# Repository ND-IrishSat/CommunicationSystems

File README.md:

# Communication Systems
Created during the fall of 2024, this is an extension to our SDR repo. This is a more updated repo where the development on the sidekiq and usrp takes place.

# Parameters
- test frequencies
    - 70cm | 418274940 Hz | 420 MHz
- Actual frequencies
    - Rx:
    - Tx:
- Hardware
    - amplifiers?
    - antennas

S-Band downlink, but we do not have permission
UHF uplink

Rylan - General liscense

Sidekiq: ports 1 and 2 are received between 50 MHz and 6 GHz
        Port 3 receive or transmit 50 MHz and 6 GHz

Copy to irishsat    
    $ scp -r ~/path/CommunicationSystems/ irishsat:~/Documents/Github/

To compile test apps in the test folder on irishsat desktop run:
        $ make BUILD_CONFIG=arm_cortex-a9.gcc7.2.1_gnueabihf
        Add clean after to clean builds
        This will build the test files in the bin folder

root@sidekiqz2:/tmp# ./rx_samples -d output --words 5000000 --rate 1000000000 --frequency 418274940

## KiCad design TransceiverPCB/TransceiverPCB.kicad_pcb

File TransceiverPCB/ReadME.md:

```
 /$$$$$$ /$$$$$$$  /$$$$$$  /$$$$$$  /$$   /$$  /$$$$$$   /$$$$$$  /$$$$$$$$                                                            
|_  $$_/| $$__  $$|_  $$_/ /$$__  $$| $$  | $$ /$$__  $$ /$$__  $$|__  $$__/                                                            
  | $$  | $$  \ $$  | $$  | $$  \__/| $$  | $$| $$  \__/| $$  \ $$   | $$                                                               
  | $$  | $$$$$$$/  | $$  |  $$$$$$ | $$$$$$$$|  $$$$$$ | $$$$$$$$   | $$                                                               
  | $$  | $$__  $$  | $$   \____  $$| $$__  $$ \____  $$| $$__  $$   | $$                                                               
  | $$  | $$  \ $$  | $$   /$$  \ $$| $$  | $$ /$$  \ $$| $$  | $$   | $$                                                               
 /$$$$$$| $$  | $$ /$$$$$$|  $$$$$$/| $$  | $$|  $$$$$$/| $$  | $$   | $$                                                               
|______/|__/  |__/|______/ \______/ |__/  |__/ \______/ |__/  |__/   |__/                                                               
                                                                                                                                        
                                                                                                                                        
                                                                                                                                        
 /$$$$$$$$                                                         /$$                                     /$$$$$$$   /$$$$$$  /$$$$$$$ 
|__  $$__/                                                        |__/                                    | $$__  $$ /$$__  $$| $$__  $$
   | $$  /$$$$$$  /$$$$$$  /$$$$$$$   /$$$$$$$  /$$$$$$$  /$$$$$$  /$$ /$$    /$$ /$$$$$$   /$$$$$$       | $$  \ $$| $$  \__/| $$  \ $$
   | $$ /$$__  $$|____  $$| $$__  $$ /$$_____/ /$$_____/ /$$__  $$| $$|  $$  /$$//$$__  $$ /$$__  $$      | $$$$$$$/| $$      | $$$$$$$ 
   | $$| $$  \__/ /$$$$$$$| $$  \ $$|  $$$$$$ | $$      | $$$$$$$$| $$ \  $$/$$/| $$$$$$$$| $$  \__/      | $$____/ | $$      | $$__  $$
   | $$| $$      /$$__  $$| $$  | $$ \____  $$| $$      | $$_____/| $$  \  $$$/ | $$_____/| $$            | $$      | $$    $$| $$  \ $$
   | $$| $$     |  $$$$$$$| $$  | $$ /$$$$$$$/|  $$$$$$$|  $$$$$$$| $$   \  $/  |  $$$$$$$| $$            | $$      |  $$$$$$/| $$$$$$$/
   |__/|__/      \_______/|__/  |__/|_______/  \_______/ \_______/|__/    \_/    \_______/|__/            |__/       \______/ |_______/ 
                                                                                                                                        
                                                                                                                                        
                                                                                                                                        
```

### Team

```
├── Communication Systems
│   ├── Rylan Paul
│   ├── Joaquin Caraveo
│   ├── Caden Niziol
│   ├── Alyssa Riter
│   ├── Anna Arnett
│   ├── Thomas Mancini

```

### To Add a New Part

> ----
>
> 1. Open a new github branch from main named `Import PART#`
> 
> 2. Download symbol, footprints, and 3d model (Ultra Librarian, Snap Magic, etc.)
>
> 3. Unzip the files
>
> 4. Structure the folder as shown for `EXAMPLE_PART_ID`
>
> 5. Put the new part folder in the `PARTS` folder
>
> 6. Copy all of the new footprints and paste them into the `LIB_IRISHSAT.pretty` folder
>
> 7. If KiCAD is open, in the footprint editor, press the referesh button
>
> 8. Open the KiCAD Symbol Editor
>
> 9. Search for `LIB_IRISHSAT`
>
> 10. Right click `LIB_IRISHSAT` and click `Import Symbol`
>
> 11. Go to your new part in the `PARTS` folder
>
> 12. Click on the `part.kicad_sym` or `part.lib` file to import it
>
> 13. Close the symbol editor and `save`
>
> 14. Open the `footprint editor`
>
> 15. Go to the newly added footprints
>
> 16. Click the `Footprint Properties` button
>
> 17. Click on the `3D Models` tab
>
> 18. Click the folder icon and navigate to your new part in the `PARTS` folder
>
> 19. Select your 3D model usually either `.stl` or `.stp` or `.step`
>
> 20. Confirm the position and rotation alignment
> 
> 21. Save and close the footprint editor
> 
> 22. Create a `Pull Request` merging your new branch `Import PART#` into `main` and assign your team lead
>
> ----

### Project File Structure

```

├── fp-info-cache
├── fp-lib-table
├── LIB_IRISHSAT.bak
├── LIB_IRISHSAT.kicad_sym                          # All Imported Symbols Library
├── LIB_IRISHSAT.pretty                             # List of all footprints from the `PARTS` folder
│   ├── ...
├── PARTS                                           # List of all parts
│   ├── EXAMPLE_PART_ID                             # Part name
│   │   ├── part.kicad_sym                          # Sybmol file
│   │   ├── part.step                               # 3D Model
│   │   └── footprints.pretty                       # Footpints
│   │       └── part.kicad_mod                      # Footprint files
|   |
│   ├── ABM8_272_T3                                 # Crystal Oscillator 12MHz for RP2040
│   │   ├── ...
│   ├── AD9218BSTZ-65                               # Analog to Digital Converter
│   │   ├── ...
│   ├── AD9763ASTZ                                  # Digital to Analog Converter
│   │   ├── ...
│   ├── ADA4940_2ACPZ_R7                            # Fully Differential Amplifier (ADC Driver)
│   │   ├── ...
│   ├── ADF4351BCPZ-RL7                             # Local Oscillator
│   │   ├── ...
│   ├── ADL5320ARKZ_R7                              # Power Amplifier
│   │   ├── ...
│   ├── ADL5375_05ACPZ_R7                           # IQ Modulator
│   │   ├── ...
│   ├── ADL5380ACPZ_R7                              # IQ Demodulator
│   │   ├── ...
│   ├── B39921B2672P810                             # Band Pass Filter (ISM 915MHz)
│   │   ├── ...
│   ├── BLM18KG601SN1D                              # Ferrite Capacitor
│   │   ├── ...
│   ├── CFR_25JB_52_43R                             # 43 Ohm Resistor ±5%
│   │   ├── ...
│   ├── DSC1001CI2-100-0000T                        # Crystal Oscillator 100MHz for FPGA
│   │   ├── ...
│   ├── QPL6220QTR7                                 # Low Noise Amplifier
│   │   ├── ...
│   ├── W25Q32JVSSIQ                                # Flash Memory QSPI
│   │   ├── ...
│   └── XC7A35T_1FTG256C                            # FPGA
│       ├── ...
├── ReadME.md                                       # ReadMe
├── sym-lib-table
├── TransceiverPCB-backups
│   ├── TransceiverPCB-2026-02-07_141501.zip
│   ├── TransceiverPCB-2026-02-08_221813.zip
│   └── TransceiverPCB-2026-02-08_225630.zip
├── TransceiverPCB.kicad_pcb                        # Main KiCAD file
├── TransceiverPCB.kicad_prl                        # Main KiCAD file
├── TransceiverPCB.kicad_pro                        # Main KiCAD file
└── TransceiverPCB.kicad_sch                        # Main KiCAD file

```

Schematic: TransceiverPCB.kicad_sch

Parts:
C1, C2, C6, C7, C26, C75, C77, C82, C87, C89, C116, C121, C122, C123, C129, C130, C131, C132, C133, C134, C135, C142, C152, C156: 0.1uF; C_0603_1608Metric
C3, C4: 22nF; C_0402_1005Metric
C5, C8, C48, C49, C51, C59: 100pF; C_0402_1005Metric
C9, C14, C15, C16, C17, C18, C19, C20, C22, C23, C30, C35, C70, C79: 100nF; C_0603_1608Metric
C10, C11, C85: 22pF; C_0402_1005Metric
C12, C29, C31, C32, C33, C34, C61: 10uF; C_0603_1608Metric
C13, C21, C24, C25, C36, C44, C45, C55, C56, C90: 1uF; C_0603_1608Metric
C27, C69, C73: 4.7uF; C_0402_1005Metric
C28: 0.1uF; C_0402_1005Metric
C38, C39: 270pF; C_0402_1005Metric
C40, C41: 91pF; C_0402_1005Metric
C42, C43: 68pF; C_0402_1005Metric
C46, C47, C50, C52, C153, C154: .1uF; C_0603_1608Metric
C53, C54: 1000pF; C_0402_1005Metric
C57, C62: 47pF; C_0402_1005Metric
C58: 6.8pF; C_0402_1005Metric
C60: 10nF; C_0402_1005Metric
C63: 2.2pF; C_0402_1005Metric
C64, C66: 53.62pF; C_0402_1005Metric
C65, C67: 350.1pF; C_0402_1005Metric
C68, C71, C74: 10uF; C_0402_1005Metric
C72, C113, C158: 47uF; C_1210_3225Metric
C76: 47uF; C_1206_3216Metric
C78: 6.8nF; C_0402_1005Metric
C80, C81: 22uF; C_1206_3216Metric
C83, C84, C127, C128: 1nF; C_0402_1005Metric
C86, C88, C155: 10pF; C_0402_1005Metric
C93, C94: 100uF; C_1210_3225Metric
C95, C96, C107, C108, C159, C160, C167, C168, C173, C174, C179, C180: 4.7uF; C_0805_2012Metric
C97, C109, C110, C111, C114, C161, C162, C163, C164, C165, C166, C169, C170, C171, C172, C175, C176, C177, C178, C181, C182, C183, C184: 0.47uF; C_0201_0603Metric
C115, C117, C141, C145: 120pF; C_0402_1005Metric
C118, C120, C126, C143, C144, C148, C149: 3.3pF; C_0402_1005Metric
C119, C125, C146, C147: 4.7pF; C_0402_1005Metric
C124: 3.3pF; C_0603_1608Metric
C138: 2700pF; C_0402_1005Metric
C139: 39nF; C_0402_1005Metric
C140: 1200pF; C_0402_1005Metric
C150, C151: 1nF; C_0603_1608Metric
D1: ESD5Z5V0; P38_SOD-523
D2, D3: LED; LED_0603_1608Metric
FL1, FL2, FL4: B39921B2672P810; Mouser Part Number 871-B39921B2672P810
IC1: QPL6220QTR7; SON50P200X200X90-9N-D; Mouser Part Number 772-QPL6220QTR7
IC2: AD9218BSTZ-65; QFP50P900X900X160-48N; Manufacturer_Part_Number AD9218BSTZ-65; Mouser Part Number 584-AD9218BSTZ-65
IC3: AD9763ASTZ; QFP50P900X900X160-48N; Manufacturer_Part_Number AD9763ASTZ; Mouser Part Number 584-AD9763ASTZ
IC4: ADF4351BCPZ-RL7; QFN50P500X500X80-33N-D; Mouser Part Number 584-ADF4351BCPZ-R7
J1: USB4085-GF-A_REVB; USB_C_Receptacle_GCT_USB4085; PARTREV B
J2, J3: RFPC-SMA27-F; GRADCONN_RFPC-SMA27-F; PARTREV 1.0
J5: Conn_01x02; JST_PH_B2B-PH-K_1x02_P2.00mm_Vertical
J6: 878321420; CONN14_878321420_MOL
L1, L33, L34: 2.2uH; IND_DFE2016_MUR
L2, L3: 120nH; L_0402_1005Metric
L4, L5, L6, L7, L8, L9, L10, L13: 27uH; L_0402_1005Metric
L11, L12, L14, L15: 10uH; L_0402_1005Metric
L16: 47nH; L_0402_1005Metric
L17, L18, L19, L20: 771.1nH; L_0402_1005Metric
L21, L22, L23, L24, L29, L30, L31, L32: 2.7nH; L_0402_1005Metric
L25, L26, L27, L28: 19nH; L_0402_1005Metric
L35: 2.7uH; L_0402_1005Metric
Q1, Q2: AO3401A; SOT-23
R1, R14, R16, R17: 50; R_0402_1005Metric
R2, R30: DNF; R_0402_1005Metric
R3, R5, R13, R20, R21, R22, R23, R24, R25, R26, R29: 1k; R_0402_1005Metric
R4, R10, R19, R27, R28, R34, R38, R40, R41, R53: 10k; R_0402_1005Metric
R6, R7, R55: 5.1k; R_0402_1005Metric
R8, R9: 27.4k; R_0402_1005Metric
R11, R12: 500; R_0402_1005Metric
R15, R18, R33, R37: 100; R_0402_1005Metric
R31: 470k; R_0402_1005Metric
R32: 54k; R_0402_1005Metric
R35: 360; R_0402_1005Metric
R36: 680; R_0402_1005Metric
R39: 3.32k; R_0402_1005Metric
R42, R43: 256; R_0402_1005Metric
R44: 2k; R_0402_1005Metric
R45, R46, R47: 33; R_0402_1005Metric
R48: 52.3k; R_0402_1005Metric
R49: 4.32k; R_0402_1005Metric
R50: 127.758k; R_0402_1005Metric
R51: 28.212k; R_0402_1005Metric
R52: 51; R_0402_1005Metric
R54: 4.7k; R_0402_1005Metric
SW1, SW2, SW4: SW_Push; SW_Tactile_SPST_NO_Straight_CK_PTS636Sx25SMTRLFS
T1: ETC1-1-13TR; ETC1-1-13TR_MCM
U1: XC7A35T-1FTG256C; FT&slash_FTG256ARTIX-7_AMD
U2, U3: W25Q32JVSSIQ; SOIC-8_5P28X5P28_WIN
U4, U14: DSC1001CI2-100.0000T; CDFN4_3P2X2P5_MCH
U5: LTC4412ES6-TRMPBF; SOT-6_S_LIT
U6: ADL5375-05ACPZ-R7; CP_24_7_ADI
U7: ADA4940-2ACPZ-R7; CP_24_7_ADI
U8: ADL5320ARKZ-R7; RK_3_ADI
U9: SC09147; QFN56_7X7_RPI
U10: AP2112K-3.3TRG1; SOT_RG1_DIO
U11, U15: TPS62840DLCR; VSON8_2P1X1P6_TEX
U12: ADL5387ACPZ-R7; CP-24-14_ADI
U13: TPS62933FDRLR; SOT5X3-8_DRL_TEX
U16: TPS62841DLCR; VSON8_2P1X1P6_TEX
X1: ABM8-272-T3; ABM8-272-T3_ABR

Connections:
+1V: C30.2, C35.2, C71.2, C93.2, C107.1, C108.1, C109.2, C110.1, C111.2, C153.1, C154.1, C158.2, C162.2, IC2.5 (REFINA), IC2.7 (REFINB), L33.1, U1.E10 (VCCBRAM), U1.F7 (VCCINT), U1.F9 (VCCINT), U1.F11 (VCCBRAM), U1.G6 (VCCINT), U1.H9 (VCCINT), U1.J6 (VCCINT), U1.K9 (VCCINT), U1.L8 (VCCINT), U7.11 (VOCM2), U7.17 (VOCM1), U16.7 (SW)
+1V1_RP2040_INTERNAL: C21.2, C22.2, C23.2, U9.23 (DVDD), U9.45 (VREG_VOUT), U9.50 (DVDD)
+1V8: C74.2, C113.2, C159.1, C160.2, C161.2, C163.1, C164.2, L34.1, U1.F8 (VCCBATT_0), U1.G8 (VCCADC_0), U1.G10 (VCCAUX), U1.J10 (VCCAUX), U1.K11 (VCCAUX), U1.L10 (VCCAUX), U11.7 (SW)
+3.3V: C36.2, C44.2, C45.2, C55.1, C56.1, C90.1, IC4.6 (VP), IC4.10 (AVDD), IC4.16 (VVCO_1), IC4.17 (VVCO_2), IC4.28 (DVDD), IC4.32 (SDVDD)
+3V: C1.1, C2.1, C68.2, C121.1, C122.1, C123.1, C129.1, C130.1, C131.1, C132.1, IC2.8 (S1), IC2.13 (VD_1), IC2.15 (VDD_1), IC2.28 (VDD_2), IC2.30 (VD_2), IC2.31 (VD_3), IC2.33 (VDD_3), IC2.46 (VDD_4), IC2.48 (VD_4), L1.1, U15.7 (SW)
+3V3: C9.2, C13.1, C14.1, C15.1, C16.1, C17.1, C18.1, C19.1, C20.1, C24.2, C28.2, C29.2, C70.2, C72.1, C75.1, C82.1, C94.1, C95.1, C96.2, C97.2, C114.1, C115.1, C116.1, C117.1, C133.1, C134.1, C135.1, C141.1, C142.1, C145.1, C152.1, C165.2, C166.1, C167.1, C168.2, C169.2, C170.1, C171.2, C172.1, C173.1, C174.2, C175.2, C176.1, C177.2, C178.1, C179.1, C180.2, C181.2, C182.1, C183.2, C184.1, D2.1 (K), D3.1 (K), IC3.16 (DVDD1), IC3.22 (DVDD2), IC3.42 (GAINCTRL), IC3.43 (REFIO), IC3.47 (AVDD), J6.2, L25.1, L26.1, L27.1, L28.1, R2.1, R4.2, R28.2, R30.1, R38.2, R40.2, R41.2, R54.1, U1.A6 (VCCO_35), U1.A16 (VCCO_15), U1.B3 (VCCO_35), U1.B13 (VCCO_15), U1.C10 (VCCO_15), U1.D7 (VCCO_35), U1.E4 (VCCO_35), U1.E14 (VCCO_15), U1.F1 (VCCO_35), U1.H15 (VCCO_15), U1.J2 (VCCO_35), U1.J12 (VCCO_15), U1.L6 (VCCO_0), U1.L16 (VCCO_14), U1.M3 (VCCO_34), U1.M13 (VCCO_14), U1.N10 (VCCO_14), U1.P7 (VCCO_14), U1.R4 (VCCO_34), U1.R14 (VCCO_14), U1.T1 (VCCO_34), U1.T11 (VCCO_14), U2.8 (VCC), U3.8 (VCC), U4.1 (*STANDBY), U4.4 (VDD), U9.1 (IOVDD), U9.10 (IOVDD), U9.22 (IOVDD), U9.33 (IOVDD), U9.42 (IOVDD), U9.43 (ADC_AVDD), U9.44 (VREG_VIN), U9.48 (USB_VDD), U9.49 (IOVDD), U10.5 (VOUT), U14.1 (*STANDBY), U14.4 (VDD)
+5V: C5.2, C6.2, C7.1, C8.1, C12.2, C25.1, C26.2, C27.2, C46.1, C47.1, C48.1, C49.1, C50.1, C51.1, C59.1, C60.1, C61.1, C69.2, C73.2, C76.2, C85.1, D1.2 (C), L16.1, Q1.2 (S), Q2.2 (S), R10.1, R31.1, R39.1, U5.6 (SENSE), U6.18 (VPS1), U6.24 (VPS2), U7.3 (VS1+), U7.4 (VS1+), U7.9 (VS2+), U7.10 (VS2+), U7.16 (VS2+), U10.1 (VIN), U11.2 (VIN), U11.3 (MODE), U11.4 (EN), U12.1 (VPA), U12.4 (VPL), U12.5 (VPL), U12.6 (VPL), U12.17 (VPB), U12.18 (VPB), U12.19 (VPX), U15.2 (VIN), U15.3 (MODE), U15.4 (EN), U16.2 (VIN), U16.3 (MODE), U16.4 (EN)
+BATT: C77.2, J5.1, R50.1, U13.3 (VIN)
+USB5V: J1.A4 (VBUS), J1.A9 (VBUS__1), J1.B4 (VBUS__2), J1.B9 (VBUS__3), Q1.3 (D), U5.1 (VIN)
/CE_ADF4351_LO: IC4.4 (CE), U9.16 (GPIO13)
/CLK1/IQCLK: IC3.18 (CLK1/IQCLK), IC3.19 (CLK2/IQRESET), R45.2
/CLK_ADF4351_LO: IC4.1 (CLK), U9.13 (GPIO10)
/CPOUT_ADF4351_LO: C138.1, C139.1, IC4.7 (CPOUT), R36.1
/D0A_ADC: IC2.35 (D0A), U1.L15 (IO_L3P_T0_DQS_PUDC_B_14)
/D0B_ADC: IC2.26 (D0B), U1.P16 (IO_L8N_T1_D12_14)
/D1A_ADC: IC2.36 (D1A), U1.M15 (IO_L3N_T0_DQS_EMCCLK_14)
/D1B_ADC: IC2.25 (D1B), U1.P15 (IO_L8P_T1_D11_14)
/D2A_ADC: IC2.37 (D2A), U1.L14 (IO_L4P_T0_D04_14)
/D2B_ADC: IC2.24 (D2B), U1.P13 (IO_L11N_T1_SRCC_14)
/D3A_ADC: IC2.38 (D3A), U1.M14 (IO_L4N_T0_D05_14)
/D3B_ADC: IC2.23 (D3B), U1.N13 (IO_L11P_T1_SRCC_14)
/D4A_ADC: IC2.39 (D4A), U1.L13 (IO_L5N_T0_D07_14)
/D4B_ADC: IC2.22 (D4B), U1.P14 (IO_L12N_T1_MRCC_14)
/D5A_ADC: IC2.40 (D5A), U1.K13 (IO_L5P_T0_D06_14)
/D5B_ADC: IC2.21 (D5B), U1.N14 (IO_L12P_T1_MRCC_14)
/D6A_ADC: IC2.41 (D6A), U1.L12 (IO_L6P_T0_FCS_B_14)
/D6B_ADC: IC2.20 (D6B), U1.R15 (IO_L9P_T1_DQS_14)
/D7A_ADC: IC2.42 (D7A), U1.M12 (IO_L6N_T0_D08_VREF_14)
/D7B_ADC: IC2.19 (D7B), U1.R16 (IO_L9N_T1_DQS_D13_14)
/D8A_ADC: IC2.43 (D8A), U1.M16 (IO_L7P_T1_D09_14)
/D8B_ADC: IC2.18 (D8B), U1.T9 (IO_L22P_T3_A05_D21_14)
/D9A_ADC_MSB: IC2.44 (D9A(MSB)), U1.N16 (IO_L7N_T1_D10_14)
/D9B_ADC_MSB: IC2.17 (D9B), U1.T10 (IO_L22N_T3_A04_D20_14)
/DAC_DB0-P1: IC3.10 (DB0-P1), U1.A8 (IO_L2P_T0_AD8P_15)
/DAC_DB0-P2: IC3.32 (DB0-P2), U1.B12 (IO_L5P_T0_AD9P_15)
/DAC_DB1-P1: IC3.9 (DB1-P1), U1.A9 (IO_L2N_T0_AD8N_15)
/DAC_DB1-P2: IC3.31 (DB1-P2), U1.B14 (IO_L8N_T1_AD10N_15)
/DAC_DB2-P1: IC3.8 (DB2-P1), U1.A10 (IO_L3N_T0_DQS_AD1N_15)
/DAC_DB2-P2: IC3.30 (DB2-P2), U1.B15 (IO_L9P_T1_DQS_AD3P_15)
/DAC_DB3-P1: IC3.7 (DB3-P1), U1.A12 (IO_L5N_T0_AD9N_15)
/DAC_DB3-P2: IC3.29 (DB3-P2), U1.B16 (IO_L10N_T1_AD11N_15)
/DAC_DB4-P1: IC3.6 (DB4-P1), U1.A13 (IO_L7P_T1_AD2P_15)
/DAC_DB4-P2: IC3.28 (DB4-P2), U1.C8 (IO_L1P_T0_AD0P_15)
/DAC_DB5-P1: IC3.5 (DB5-P1), U1.A14 (IO_L7N_T1_AD2N_15)
/DAC_DB5-P2: IC3.27 (DB5-P2), U1.C9 (IO_L1N_T0_AD0N_15)
/DAC_DB6-P1: IC3.4 (DB6-P1), U1.A15 (IO_L9N_T1_DQS_AD3N_15)
/DAC_DB6-P2: IC3.26 (DB6-P2), U1.C11 (IO_L11P_T1_SRCC_15)
/DAC_DB7-P1: IC3.3 (DB7-P1), U1.B9 (IO_L3P_T0_DQS_AD1P_15)
/DAC_DB7-P2: IC3.25 (DB7-P2), U1.E16 (IO_L17P_T2_A26_15)
/DAC_DB8-P1: IC3.2 (DB8-P1), U1.B10 (IO_L4P_T0_15)
/DAC_DB8-P2: IC3.24 (DB8-P2), U1.E15 (IO_L18N_T2_A23_15)
/DAC_DB9-P1_(MSB): IC3.1 (DB9-P1_(MSB)), U1.B11 (IO_L4N_T0_15)
/DAC_DB9-P2_(MSB): IC3.23 (DB9-P2_(MSB)), U1.E13 (IO_L13N_T2_MRCC_15)
/DATA_ADF4351_LO: IC4.2 (DATA), U9.14 (GPIO11)
/DEMOD_IN1+: R13.2, R20.2, U7.24 (IN1+)
/DEMOD_IN1-: R21.2, R24.1, U7.1 (IN1-)
/DEMOD_IN2+: R22.2, R25.1, U7.6 (IN2+)
/DEMOD_IN2-: R23.2, R26.1, U7.7 (IN2-)
/DEMOD_RFIN: C53.1, L3.1, U12.21 (RFIN)
/DEMOD_RFIP: C54.1, L2.2, U12.22 (RFIP)
/DEMOD_RF_IN: FL2.4 (OUTPUT), T1.2
/ENCA: IC2.14 (ENCB), IC2.47 (ENCA), R47.1
/FPGA_OSCILLATOR_100MHZ: U1.P10 (IO_L14P_T2_SRCC_14), U4.3 (OUT)
/I+ADC_IN: C43.1, IC2.2 (AINA), L12.2, R12.1
/I-ADC_IN: C43.2, IC2.3 (~AINA), L11.2, R12.2
/IBBN: C65.2, L18.2, R15.2, U6.22 (IBBN)
/IBBP: C65.1, L17.2, R15.1, U6.21 (IBBP)
/IOUT+: C33.1, U7.12 (OUT2+)
/IOUT-: C34.1, U7.13 (OUT2-)
/IOUTA1: C64.1, IC3.46 (IOUTA1), L17.1, R1.1
/IOUTA2: C66.2, IC3.39 (IOUTA2), L20.1, R17.2
/IOUTB1: C64.2, IC3.45 (IOUTB1), L18.1, R14.2
/IOUTB2: C66.1, IC3.40 (IOUTB2), L19.1, R16.1
/LD_ADF4351_LO: IC4.25 (LD), U9.17 (GPIO14)
/LE_ADF4351_LO: IC4.3 (LE), U9.15 (GPIO12)
/LNA_IN: FL4.4 (OUTPUT), IC1.2 (RF_IN)
/LNA_OUT: FL2.1 (INPUT), IC1.7 (RF_OUT)
/LOIN_demod: C151.2, U12.9 (LOIN)
/LOIN_mod: C127.2, U6.4 (LOIN)
/LOIP_demod: C150.2, U12.8 (LOIP)
/LOIP_mod: C128.2, U6.3 (LOIP)
/LO_A_OUT+: C118.2, IC4.12 (RFOUTA+), L21.2, L25.2, R33.1
/LO_A_OUT-: C124.1, IC4.13 (RFOUTA-), L23.2, L26.2, R33.2
/LO_B_OUT+: C143.2, IC4.14 (RFOUTB+), L28.2, L29.2, R37.1
/LO_B_OUT-: C144.1, IC4.15 (RFOUTB-), L27.2, L30.2, R37.2
/MOD_OUT: C57.1, U6.16 (RFOUT)
/MUXOUT_ADF4351_LO: IC4.30 (MUXOUT), U9.27 (GPIO16)
/PA_IN: C57.2, C58.1, U8.1 (RFIN)
/PA_OUT: C62.2, FL1.1 (INPUT)
/PDBRF_ADF4351_LO: IC4.26 (PDBRF), U9.18 (GPIO15)
/Q+ADC_IN: C42.1, IC2.11 (AINB), L14.2, R11.2
/Q-ADC_IN: C42.2, IC2.10 (~AINB), L15.2, R11.1
/QBBN: C67.1, L19.2, R18.1, U6.9 (QBBN)
/QBBP: C67.2, L20.2, R18.2, U6.10 (QBBP)
/QOUT+: C31.1, U7.18 (OUT1+)
/QOUT-: C32.1, U7.19 (OUT1-)
/QSPI_SCLK_FPGA: U1.E8 (CCLK_0), U2.6 (CLK)
/QSPI_SCLK_RP2040: U3.6 (CLK), U9.52 (SQPI_SCLK)
/QSPI_SD0_FPGA: U1.T12 (IO_L15N_T2_DQS_DOUT_CSO_B_14), U2.5 (DI(IO0))
/QSPI_SD0_RP2040: U3.5 (DI(IO0)), U9.53 (SQPI_SD0)
/QSPI_SD1_FPGA: U1.J14 (IO_L1N_T0_D01_DIN_14), U2.2 (DO(IO1))
/QSPI_SD1_RP2040: U3.2 (DO(IO1)), U9.55 (SQPI_SD1)
/QSPI_SD2_FPGA: U1.K15 (IO_L2P_T0_D02_14), U2.3 (/WP(IO2))
/QSPI_SD2_RP2040: U3.3 (/WP(IO2)), U9.54 (SQPI_SD2)
/QSPI_SD3_FGPA: U1.K16 (IO_L2N_T0_D03_14), U2.7 (/HOLD_OR_/RESET(IO3))
/QSPI_SD3_RP2040: U3.7 (/HOLD_OR_/RESET(IO3)), U9.51 (SQPI_SD3)
/QSPI_SS_FPGA: R29.1, R30.2, U1.R13 (IO_L16P_T2_CSI_B_14), U2.1 (/CS)
/QSPI_SS_RP2040: R2.2, R5.1, U3.1 (/CS), U9.56 (SQPI_SS_N)
/REFIN_ADF4351_OSCILLATOR: C84.2, IC4.29 (REFIN)
/RUN: R4.1, SW1.2, U9.26 (RUN)
/SMA_RX_OUT: FL4.1 (INPUT), J3.1
/SMA_TX_IN: FL1.4 (OUTPUT), J2.1
/USB_BOOT: R5.2, R29.2, SW2.2, SW4.2
/USB_D+: J1.A6 (DP1), J1.B6 (DP2), R8.1
/USB_D-: J1.A7 (DN1), J1.B7 (DN2), R9.1
/VTUNE_ADF4351_LO: C140.1, IC4.20 (VTUNE), R36.2
/WRT1/IQWRT: IC3.17 (WRT1/IQWRT), IC3.20 (WRT2/IQSEL), R46.2
/XIN_RP2040: C11.1, U9.20 (XIN), X1.1 (IN)
/XOUT_RP2040: R3.2, U9.21 (XOUT)
FPGA_RESET: R28.1, U1.L9 (PROGRAM_B_0), U9.2 (GPIO0)
FPGA_TCK: J6.6, R53.1, U1.L7 (TCK_0)
FPGA_TDI: J6.10, R38.1, U1.N7 (TDI_0)
FPGA_TDO: J6.8, U1.N8 (TDO_0)
FPGA_TMS: J6.4, R40.1, U1.M7 (TMS_0)
GND: C1.2, C2.2, C3.2, C4.2, C5.1, C6.1, C7.2, C8.2, C9.1, C10.2, C11.2, C12.1, C13.2, C14.2, C15.2, C16.2, C17.2, C18.2, C19.2, C20.2, C21.1, C22.1, C23.1, C24.1, C25.2, C26.1, C27.1, C28.1, C29.1, C30.1, C35.1, C36.1, C44.1, C45.1, C46.2, C47.2, C48.2, C49.2, C50.2, C51.2, C52.1, C55.2, C56.2, C58.2, C59.2, C60.2, C61.2, C63.2, C68.1, C69.1, C70.1, C71.1, C72.2, C73.1, C74.1, C75.2, C76.1, C77.1, C78.1, C80.1, C81.1, C82.2, C85.2, C86.2, C87.2, C88.2, C89.2, C90.2, C93.1, C94.2, C95.2, C96.1, C97.1, C107.2, C108.2, C109.1, C110.2, C111.1, C113.1, C114.2, C115.2, C116.2, C117.2, C118.1, C119.1, C120.1, C121.2, C122.2, C123.2, C124.2, C125.2, C126.2, C129.2, C130.2, C131.2, C132.2, C133.2, C134.2, C135.2, C138.2, C140.2, C141.2, C142.2, C143.1, C144.2, C145.2, C146.1, C147.2, C148.1, C149.2, C152.2, C153.2, C154.2, C155.2, C156.2, C158.1, C159.2, C160.1, C161.1, C162.1, C163.2, C164.1, C165.1, C166.2, C167.2, C168.1, C169.1, C170.2, C171.1, C172.2, C173.2, C174.1, C175.1, C176.2, C177.1, C178.2, C179.2, C180.1, C181.1, C182.2, C183.1, C184.2, D1.1 (A), FL1.2 (GROUND_1), FL1.3 (GROUND_2), FL1.5 (GROUND_3), FL2.2 (GROUND_1), FL2.3 (GROUND_2), FL2.5 (GROUND_3), FL4.2 (GROUND_1), FL4.3 (GROUND_2), FL4.5 (GROUND_3), IC1.9 (GND), IC2.1 (GND_1), IC2.9 (S2), IC2.12 (GND_2), IC2.16 (GND_3), IC2.27 (GND_4), IC2.29 (GND_5), IC2.32 (GND_6), IC2.34 (GND_7), IC2.45 (GND_8), IC3.15 (DCOM1), IC3.21 (DCOM2), IC3.38 (ACOM), IC4.8 (CPGND), IC4.9 (AGND), IC4.11 (AGNDVCO_1), IC4.18 (AGNDVCO_2), IC4.21 (AGNDVCO_3), IC4.27 (DGND), IC4.31 (SDGND), IC4.33 (EXPOSED_PAD_(GND)), J1.A1 (GND), J1.A12 (GND1), J1.B1 (GND2), J1.B12 (GND3), J1.S1 (SHELL), J1.S2 (SHELL1), J1.S3 (SHELL2), J1.S4 (SHELL3), J2.G1, J2.G2, J2.G3, J2.G4, J3.G1, J3.G2, J3.G3, J3.G4, J5.2, J6.1, J6.3, J6.5, J6.7, J6.9, J6.11, L2.1, L3.2, R1.2, R6.2, R7.1, R14.1, R16.2, R17.1, R34.2, R35.2, R44.2, R48.1, R49.1, R51.2, R52.2, R53.2, R55.2, SW1.1, SW2.1, SW4.1, T1.1, U1.A1 (GND), U1.A11 (GND), U1.B8 (GND), U1.C5 (GND), U1.C15 (GND), U1.D2 (GND), U1.D12 (GND), U1.E9 (GND), U1.F6 (GND), U1.F10 (GND), U1.F16 (GND), U1.G3 (GND), U1.G7 (GNDADC_0), U1.G9 (GND), U1.G13 (GND), U1.H6 (GND), U1.H7 (VREFN_0), U1.H8 (VP_0), U1.J7 (VN_0), U1.J8 (VREFP_0), U1.J9 (GND), U1.J11 (GND), U1.K4 (GND), U1.K6 (GND), U1.K7 (DXN_0), U1.K8 (DXP_0), U1.K14 (GND), U1.L1 (GND), U1.L11 (GND), U1.M8 (GND), U1.M10 (M1_0), U1.M11 (M2_0), U1.N5 (GND), U1.N15 (GND), U1.P2 (GND), U1.P12 (GND), U1.R9 (GND), U1.T6 (GND), U1.T16 (GND), U2.4 (GND), U3.4 (GND), U4.2 (GND), U5.2 (GND), U5.3 (CTL), U6.2 (COMM), U6.5 (COMM), U6.6 (NC), U6.7 (NC), U6.8 (COMM), U6.11 (COMM), U6.12 (COMM), U6.13 (NC), U6.14 (COMM), U6.15 (NC), U6.17 (COMM), U6.19 (COMM), U6.20 (COMM), U6.23 (COMM), U6.25 (EP), U7.15 (VS2-), U7.21 (VS1-), U7.22 (VS1-), U7.HTAB (EPAD), U8.2 (GND), U9.19 (TESTEN), U9.57 (GND), U10.2 (GND), U11.1 (GND), U11.5 (VSET), U12.2 (COM), U12.7 (CML), U12.10 (CML), U12.11 (CML), U12.12 (COM), U12.20 (CMRF), U12.23 (CMRF), U12.24 (CMRF), U12.25 (GND), U13.1 (RT), U13.4 (GND), U14.2 (GND), U15.1 (GND), U16.1 (GND), X1.2 (GND), X1.4 (GND)
LNA_ShutDown: IC1.6 (SHUT_DOWN), U9.34 (GPIO22)
MODULATOR_DSOP: U6.1 (DSOP), U9.30 (GPIO19)
unnamed: C3.1, R42.2
unnamed: C4.1, R43.2
unnamed: C31.2, L8.1
unnamed: C32.2, L5.1
unnamed: C33.2, L7.1
unnamed: C34.2, L4.1
unnamed: C38.1, L8.2, L13.1
unnamed: C38.2, L5.2, L9.1
unnamed: C39.1, L7.2, L10.1
unnamed: C39.2, L4.2, L6.1
unnamed: C40.1, L13.2, L14.1
unnamed: C40.2, L9.2, L15.1
unnamed: C41.1, L10.2, L12.1
unnamed: C41.2, L6.2, L11.1
unnamed: C53.2, T1.5
unnamed: C54.2, T1.3
unnamed: C83.2, C84.1, R52.1
unnamed: C119.2, L21.1, L22.2
unnamed: C120.2, C128.1, L22.1
unnamed: C125.1, L23.1, L24.2
unnamed: C126.1, C127.1, L24.1
unnamed: C139.2, R35.1
unnamed: C146.2, L29.1, L31.2
unnamed: C147.1, L30.1, L32.2
unnamed: C148.2, C150.1, L31.1
unnamed: C149.1, C151.1, L32.1
unnamed: D2.2 (A), R19.2
unnamed: D3.2 (A), R27.2
unnamed: IC1.1 (VBIAS), R39.2
unnamed: C52.2, IC2.4 (DFS/GAIN), IC2.6 (REFOUT)
unnamed: IC3.44 (FSADJ1), R43.1, R44.1
unnamed: IC3.41 (FSADJ2), R42.1
unnamed: IC3.48 (MODE), R41.1
unnamed: IC4.22 (RSET), R55.1
unnamed: C86.1, C87.1, IC4.19 (TEMP)
unnamed: C155.1, C156.1, IC4.23 (VCOM)
unnamed: C88.1, C89.1, IC4.24 (VREF)
unnamed: J1.A5 (CC1), R6.1
unnamed: J1.B5 (CC2), R7.2
unnamed: Q1.1 (G), U5.5 (GATE)
unnamed: C80.2, C81.2, L35.2, Q2.3 (D), R32.2
unnamed: Q2.1 (G), R31.2, U5.4 (STAT)
unnamed: R46.1, U1.C12 (IO_L11N_T1_SRCC_15)
unnamed: R45.1, U1.C13 (IO_L12N_T1_MRCC_15)
unnamed: R27.1, U1.H10 (DONE_0)
unnamed: R19.1, U1.K10 (INIT_B_0)
unnamed: R47.2, U1.N12 (IO_L13N_T2_MRCC_14)
unnamed: R54.2, U1.M9 (M0_0)
unnamed: R24.2, U7.2 (FB1+)
unnamed: R13.1, U7.23 (FB1-)
unnamed: R26.2, U7.8 (FB2+)
unnamed: R25.2, U7.5 (FB2-)
unnamed: C62.1, C63.1, L16.2, U8.3 (RFOUT)
unnamed: R9.2, U9.46 (USB_DM)
unnamed: R8.2, U9.47 (USB_DP)
unnamed: R10.2, U10.3 (EN)
unnamed: L34.2, U11.8 (VOS)
unnamed: R22.1, U12.14 (IHI)
unnamed: R23.1, U12.13 (ILO)
unnamed: R20.1, U12.16 (QHI)
unnamed: R21.1, U12.15 (QLO)
unnamed: C79.2, U13.6 (BST)
unnamed: R50.2, R51.1, U13.2 (EN)
unnamed: R32.1, R34.1, U13.8 (FB)
unnamed: C78.2, U13.7 (SS)
unnamed: C79.1, L35.1, U13.5 (SW)
unnamed: C83.1, U14.3 (OUT)
unnamed: L1.2, U15.8 (VOS)
unnamed: R48.2, U15.5 (VSET)
unnamed: L33.2, U16.8 (VOS)
unnamed: R49.2, U16.5 (VSET)
unnamed: C10.1, R3.1, X1.3 (OUT)
SPI0_CS_RP2040_FPGA: U1.E3 (IO_L11P_T1_SRCC_35), U9.7 (GPIO5)
SPI0_MISO_RP2040_FPGA: U1.F5 (IO_L13P_T2_MRCC_35), U9.6 (GPIO4)
SPI0_MOSI_RP2040_FPGA: U1.E5 (IO_L13N_T2_MRCC_35), U9.5 (GPIO3)
SPI0_SCK_RP2040_FPGA: U1.D4 (IO_L12P_T1_MRCC_35), U9.4 (GPIO2)

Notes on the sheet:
2xLO Frequency
Pin4 -> REFOUT indicates 2s complement and 2Vpp
Master Mode
Line must be 200 mils after C58
350 mils
Pin 29 <- Oscillator Can it use the 100MHz?
power bypass capacitors must be electrically as close as possible
FPGA
Decoupling Capacitors
1.9 MHz LPF MOD OUTPUT TO ADC
This is +5V but not too clean
Decoupling capacitors place as close to pin as possible
Connect pins to bank 15
JTAG Programmer
9 Thermal Vias to GND
3rd harmonic filter, LO output to demodulator
USB to +3V
Ask Chisum about ENC pins for ADC and CLK pins for DAC
USB to +3V3
Disable pin able to be left floating due to internal pull up network
100 mils
RP2040
Targets 5.12V ± 2%
USB to +1V8
POWER AND USB
Connect pins to bank 14
USB to +1V
RSET
75 mils
7.4V LiPo
FPGA Decoupling
DAC to Mod LPF (10 MHz 3db)
3rd harmonic filter, LO output to modulator
Battery will be used as long as it is at least 20mV more than USB
PLL Filter between LO pin 7 and 20
200 mils
Either 3A or 5A limit USB
FPGA Flash
Place as close as possible to FPGA
Vstart = 6.6v Vstop = 6.2v

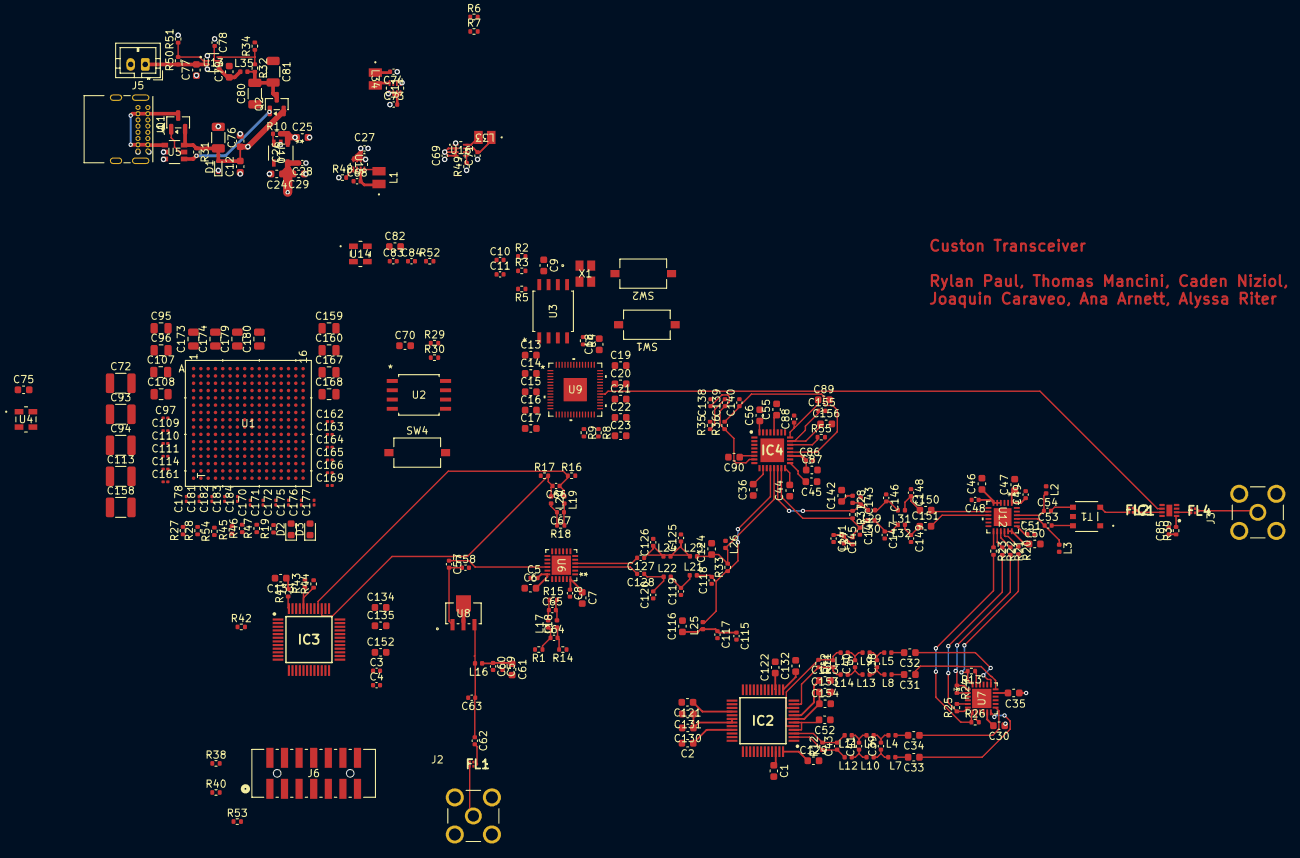
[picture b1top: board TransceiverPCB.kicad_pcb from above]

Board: 6 copper layers, 296 parts (0 on the bottom side), 203 nets.

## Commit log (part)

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2024-09-13 Setup
2024-09-22 Added libsidekiq SDK v4.18.0
2024-09-22 added test folder
2024-09-24 Test C notes
2024-09-24 edit
2024-09-26 undo readme
2024-09-26 Added sidekiq samples and python parsing script
2024-09-29 Parse rx_samples.c data
2024-09-29 transmit.py
2024-09-29 small update to parsesamples.py
2024-10-01 Readme
2024-10-02 Music!
2024-10-03 receive script
2024-10-03 receive.py updated
2024-10-03 PArse
2024-10-03 samples file
2024-10-03 Receive graph
2024-10-06 Parsesamples
2024-10-06 New receive.py script
2024-10-10 added receive.py yay
2024-10-10 Create client.c
    Adding our socket script from last year to this repo
2024-10-10 New samples
2024-10-10 SDR Test
2024-10-13 More tests
2024-10-15 Graphing now works in SDR folder
2024-10-15 update receive py
2024-10-29 hello world script
2024-10-29 Makefile changes
2024-11-08 chisum talk
2024-11-13 Updated skiq_helloworld
2024-11-14 SDR trying to transmit words, fixed USRP parse samples
2024-11-14 Updated skiq_helloworld and receive and imported signal processing
2024-11-14 SDR New file strcture
2024-11-14 Signals processing path USRP
2024-11-17 Abstracted signal processing library
2024-11-17 Func copy
2024-11-17 Implemented a stack based ring buffer and created a test program to validate functionality.
2024-11-23 Changed RingBuffer implementation to have functions copy data to a passed pointer and instead return error/success codes. Updated test file accordingly.
2025-09-11 small changes
2026-02-09 Kicad project created
    - added symbols to a library LIB_IRISHSAT
    - added footprints to a library LIB_IRISHSAT
    - added a readme
    - ALL DEVELOPMENT FROM HERE WILL BE ON ONES OWN BRANCH
    - We can do merge requests
2026-02-09 Updated Readme, added parts
    - 3d models were selected
    - basic components dropped onto the schematic
2026-02-09 Added USB-C
2026-02-09 Starting KiCAD
    - Connected RP2040 to Flash
    - Connected USB to RP2040
    - Connected 12MHz crystal oscillator to RP2040
    - Basic connections between many of the RF components
    - Placed NC and GND
    - Updated symbols to have some descriptions
2026-02-10 Finished RP2040 power supply
    - power of RP2040
2026-02-10 Diode Fix
2026-02-11 Add a git ignore
2026-02-11 Updated .gitignore
2026-02-11 Added the AD__87 Demod
2026-02-11 Removed old DEMOD
2026-02-11 .gitignore
2026-02-11 Test
    Added text
2026-02-11 Git ignore update
2026-02-11 Added some SPI on FPGA and RP2040
2026-02-13 Added Balun (ETC1-1-13)
    -Added balun to parts list
    -Added footprints and symbols
2026-02-13 Connected demod to FDA to LPF
    - connected BPF to demod with balun
    - connected demod to FDA, still need to establish Vocm
    - FDA output to LPF corner freq. 1.9 MHz
    - connected REFOUT of ADC to pin 4, indicating Vpp of 2V and output data using two's complement
2026-02-15 Added some images and comments
2026-02-16 LO Connections
    -Connected LO to RP2040
    -Connected to power
    -Decoupled
    -Looking into loop filter
2026-02-17 Modulator and Power Amplifier Complete
    Completed mod and PA
    Might need to change LO input and DAC filter - review changes
2026-02-18 Added some comments, power rail for modulator
2026-02-18 FPGA
    - added 1.8V LDO
    - added 1.0V LDO
    - VCCO pins on FPGA
    - QSPI Flash memory for FPGA
    - Oscillator for FPGA
    - Lots of decoupling capacitors
2026-02-20 Filter LO to DAC, ADC/DAC power pins
    Created filter from LO to DAC
    Wired ADC and DAC power pins
2026-02-24 Added +3V and LDO
2026-02-26 Vocm on ADC and Bias on the ADC driver
    - Vocm on ADC driver set to +1V instead of +1v1
    - rearranged some ADC pins DFS/GAIN and REFOUT are now closer
2026-02-26 Added PLL Filter for LO
    -Added PLL filter for LO between pins 7 and 20
    -Still need to look into values and how they impact frequency (if at all)
2026-02-27 Filter from LO to demod
    3rd and 5th harmonic filter from LO to demod
2026-02-27 DAC notes, caps notes
2026-02-27 DAC stuff
2026-02-28 The DAC may be all done...
2026-03-01 Added footprints, label for DAC to mod
2026-03-01 ADC Misc pins
    ask Chisum about demod to adc load resistance
2026-03-02 FPGA Footprint edits
2026-03-03 FPGA and Power
    - updated FPGA decoupling capacitors
    - used datasheet values and footprints
    - uses exact part numbers
    - updated power system to use some buck converters instead of LDOs due to higher current handling and better power efficiency
2026-03-03 Wire adjust
2026-03-03 Power management
    - added a power switch from USB to 7.4V Lipo if present
    - steps down 7.4v Lipo to +5V
2026-03-03 Wired ADF4351 LO Pins
    -Finished PLL Filter
    -Finished most pin connections
2026-03-03 Revert "Wired ADF4351 LO Pins"
    This reverts commit b407693ae4d0103785a8725409ab8d4f8a73114a.
2026-03-03 Completed ADF4153 LO Inputs
    -Wired LO Inputs
    -Finished and connected PLL filter
    -Still need to look into clock
2026-03-04 ADC data pins to FPGA
    connected all adc data pins to fpga bank 14
2026-03-05 LO GPIO Pins connected to RP2040
    -Connected LO GPIO pins to RP2040
2026-03-05 no connect many FPGA pins
2026-03-06 Added 100MHz Crystal Oscillator for LO
    -Added 100MHz crystal oscillator for LO REFin
2026-03-06 New connector
2026-03-16 LNA complete
    completed LNA pins, shutdown to pi, VREF set based on datasheet
2026-03-16 Updated some FPGA pins
2026-03-16 FINISHED FPGA Pins
2026-03-17 Added some changes for interpretability
2026-03-17 Adding the rest of the files
2026-03-18 Fixed ERC Errors
    Fixed ERC Errors:
    -Changed IC footprints so that every GND pin is set to PASSIVE
    - ADC Driver footprint VOCM pins set to inputs
2026-03-24 Began PCB
    Filled in footprints for components, and began organization of PCB footprints
2026-03-24 Grouped Together the Different Parts
    I separated all the capacitors and resistors into the groups with the modules that they belong with
2026-03-24 Began work on pcb layout
    usb and battery modules done, need work on power plane and voltage regulators
2026-03-24 done with power
    finished power
2026-03-25 Somewhat routed ADC, LPF, and ADC Driver
    -Somewhat routed ADC
    -ADC Driver
    -Made LPF filter
2026-03-25 First Draft of PCB
    Its pretty bad (oh well)
2026-03-25 some prelim files
